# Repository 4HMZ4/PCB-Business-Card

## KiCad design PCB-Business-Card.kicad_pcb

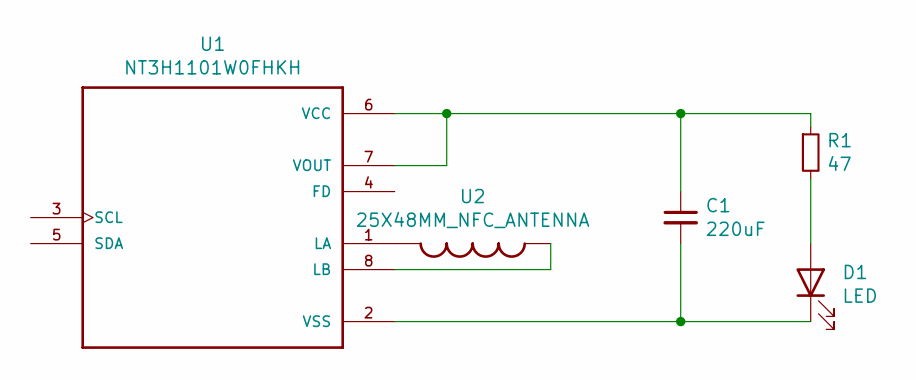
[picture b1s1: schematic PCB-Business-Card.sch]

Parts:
C1: 220uF; C_0603_1608Metric_Pad1.05x0.95mm_HandSolder
D1: LED; LED_0805_2012Metric_Pad1.15x1.40mm_HandSolder
R1: 47; R_0603_1608Metric_Pad1.05x0.95mm_HandSolder
U1: NT3H1101W0FHKH; IC_NT3H1101W0FHKH
U2: 25X48MM_NFC_ANTENNA

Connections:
unnamed: C1.1, R1.1, U1.6 (VCC), U1.7 (VOUT)
unnamed: C1.2, D1.1 (K), U1.2 (VSS)
unnamed: D1.2 (A), R1.2
unnamed: U1.1 (LA), U2.1
unnamed: U1.8 (LB), U2.2

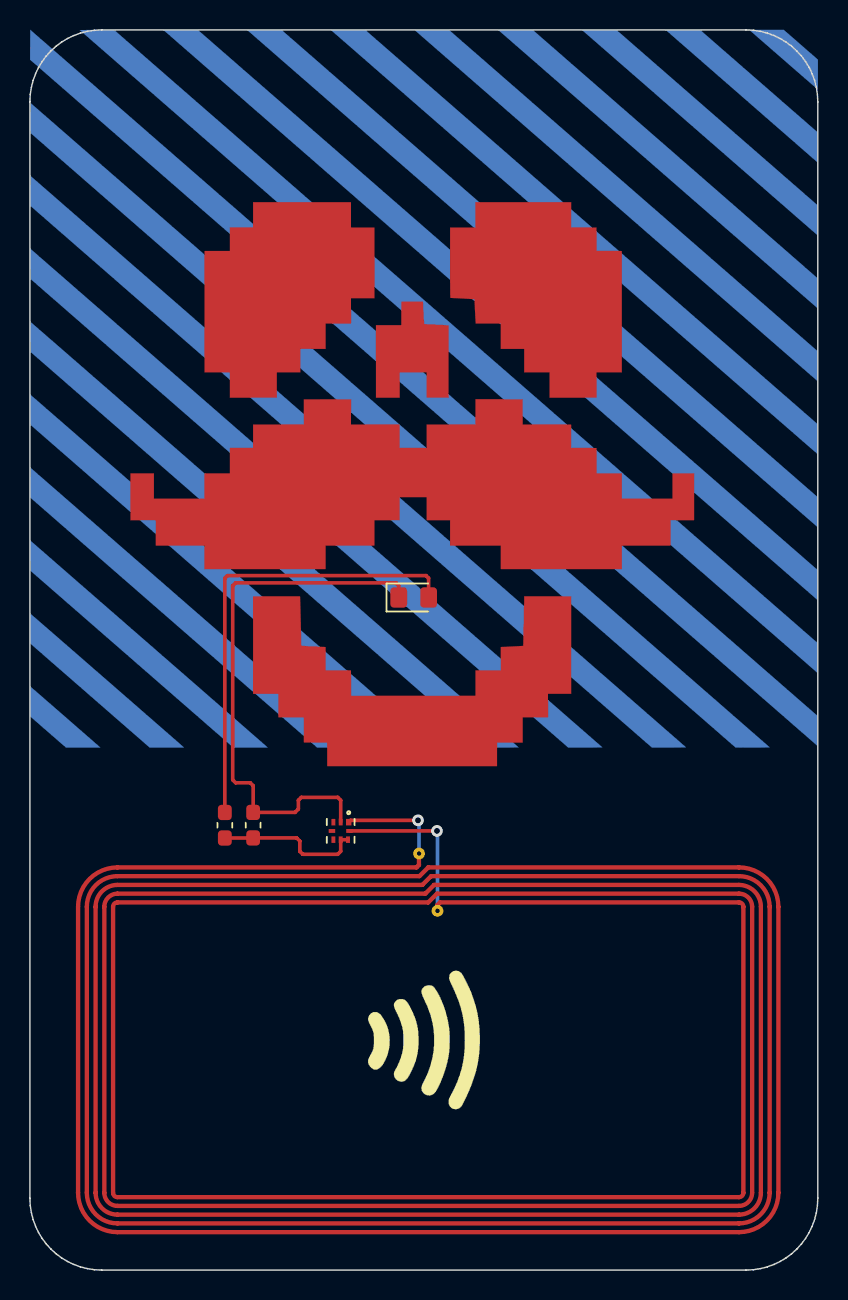
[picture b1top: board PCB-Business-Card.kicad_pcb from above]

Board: 2 copper layers, 54.0 x 85.0 mm, 6 parts (0 on the bottom side), 5 nets.

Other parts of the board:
Ref**: Val**; pcb-artwork

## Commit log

2020-10-03 PCB complete. Need to fab the PCB and test
